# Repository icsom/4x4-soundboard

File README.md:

# DIY Arduino 4x4-Soundboard
![breadboard-picture][arduino_breadboard]
### simple approach to build a soundboard which plays sounds from sd-card

hardware:
* Arduino / Leonardo
* DFPlayer mini
* 4x4 matrix keypad
* 1 resistor (1K Ohm 0.25W)
* 1 polarized capacitor (not necessarily - 100nF 6.3V) 
* speaker (<=3W)
* sd-card (<=32GB - FAT/FAT32)

tested with:
* Arduino Uno R3 (SoftwareSerial)
* Leonardo Micro Pro (Serial1)

### PCB for Arduino Pro-Mini with 20# 6x6mm tactile switches
<a href="https://oshpark.com/shared_projects/dLmm6mMB"></img></a>

[arduino_breadboard]: https://github.com/icsom/4x4-soundboard/blob/master/pictures/arduino_breadboard.jpg "Arduino Uno R3 & DFPlayer mini & 4x4 Keypad"

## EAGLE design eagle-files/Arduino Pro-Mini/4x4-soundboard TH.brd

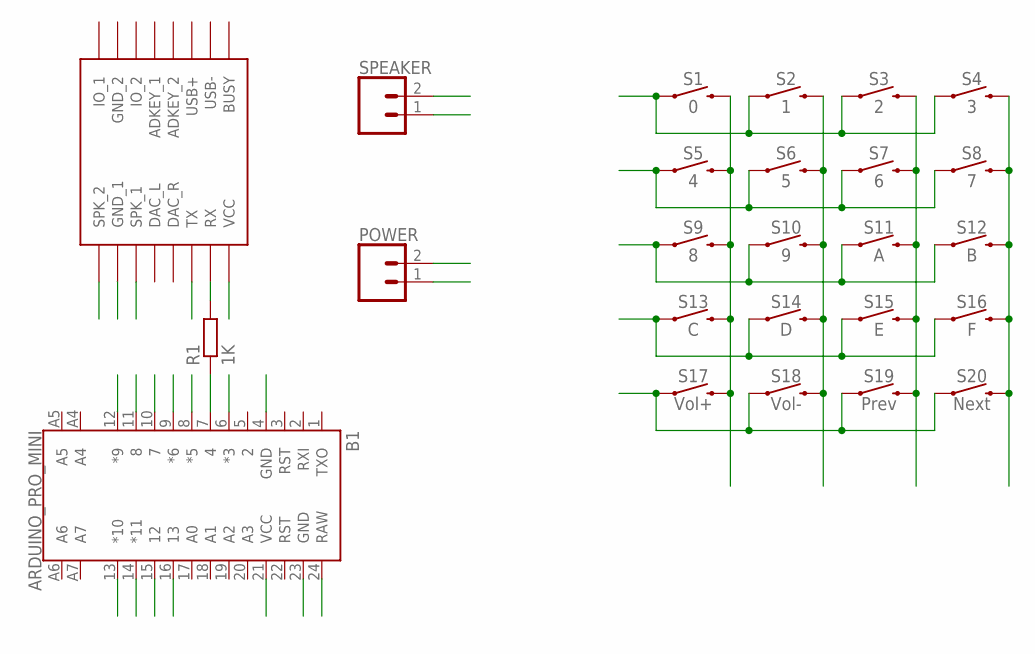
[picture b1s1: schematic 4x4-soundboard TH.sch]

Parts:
B1: ARDUINO_PRO_MINI
POWER: CONN_02; 1X02
R1: 1K; 0207/10
S1: 0; TACTILE_SWITCH_PTH_6.0MM
S2: 1; TACTILE_SWITCH_PTH_6.0MM
S3: 2; TACTILE_SWITCH_PTH_6.0MM
S4: 3; TACTILE_SWITCH_PTH_6.0MM
S5: 4; TACTILE_SWITCH_PTH_6.0MM
S6: 5; TACTILE_SWITCH_PTH_6.0MM
S7: 6; TACTILE_SWITCH_PTH_6.0MM
S8: 7; TACTILE_SWITCH_PTH_6.0MM
S9: 8; TACTILE_SWITCH_PTH_6.0MM
S10: 9; TACTILE_SWITCH_PTH_6.0MM
S11: A; TACTILE_SWITCH_PTH_6.0MM
S12: B; TACTILE_SWITCH_PTH_6.0MM
S13: C; TACTILE_SWITCH_PTH_6.0MM
S14: D; TACTILE_SWITCH_PTH_6.0MM
S15: E; TACTILE_SWITCH_PTH_6.0MM
S16: F; TACTILE_SWITCH_PTH_6.0MM
S17: Vol+; TACTILE_SWITCH_PTH_6.0MM
S18: Vol-; TACTILE_SWITCH_PTH_6.0MM
S19: Prev; TACTILE_SWITCH_PTH_6.0MM
S20: Next; TACTILE_SWITCH_PTH_6.0MM
SPEAKER: CONN_02; 1X02
U$1: DFPLAYER

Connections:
5V: B1.21 (VCC), U$1.VCC
COL1: B1.13 (*10), S1.3 (2), S5.3 (2), S9.3 (2), S13.3 (2), S17.3 (2)
COL2: B1.14 (*11), S2.3 (2), S6.3 (2), S10.3 (2), S14.3 (2), S18.3 (2)
COL3: B1.15 (12), S3.3 (2), S7.3 (2), S11.3 (2), S15.3 (2), S19.3 (2)
COL4: B1.16 (13), S4.3 (2), S8.3 (2), S12.3 (2), S16.3 (2), S20.3 (2)
GND: B1.4 (GND), B1.23 (GND), POWER.2, U$1.GND_1
unnamed: B1.7 (4), R1.1
ROW1: B1.8 (*5), S1.1, S2.1, S3.1, S4.1
ROW2: B1.9 (*6), S5.1, S6.1, S7.1, S8.1
ROW3: B1.10 (7), S9.1, S10.1, S11.1, S12.1
ROW4: B1.11 (8), S13.1, S14.1, S15.1, S16.1
ROW5: B1.12 (*9), S17.1, S18.1, S19.1, S20.1
SPK+: SPEAKER.1, U$1.SPK1 (SPK_1)
SPK-: SPEAKER.2, U$1.SPK2 (SPK_2)
SRX: B1.6 (*3), U$1.TX
STX: R1.2, U$1.RX
VIN: B1.24 (RAW), POWER.1

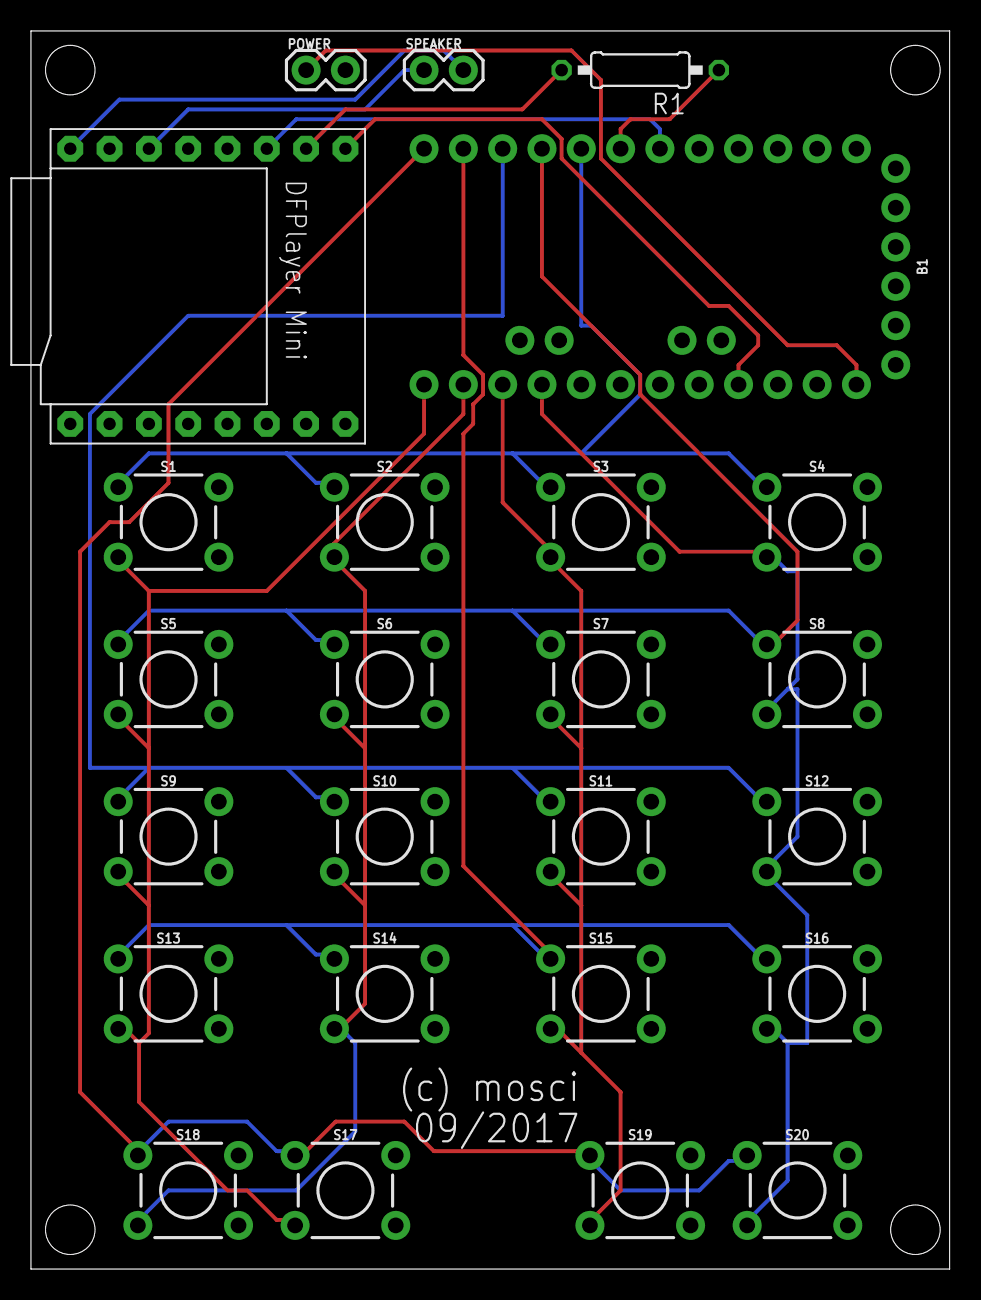
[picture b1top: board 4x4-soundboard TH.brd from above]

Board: 2 copper layers, 59.4 x 80.0 mm, 25 parts (0 on the bottom side), 17 nets.

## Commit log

2017-09-18 added eagle files
2017-09-18 readme
2017-09-18 restructured eagle-files
2017-09-18 added arduino-projekt
2017-09-18 replaced SMT with TH
2017-09-18 added pcb-picture
2017-09-19 added pictures
2017-09-19 changed pictures
2017-09-19 changed file name due to errors in IDE

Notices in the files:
parts and their libraries:
SparkFun-Boards: Licensing: Creative Commons ShareAlike 4.0 International - https://creativecommons.org/licenses/by-sa/4.0
